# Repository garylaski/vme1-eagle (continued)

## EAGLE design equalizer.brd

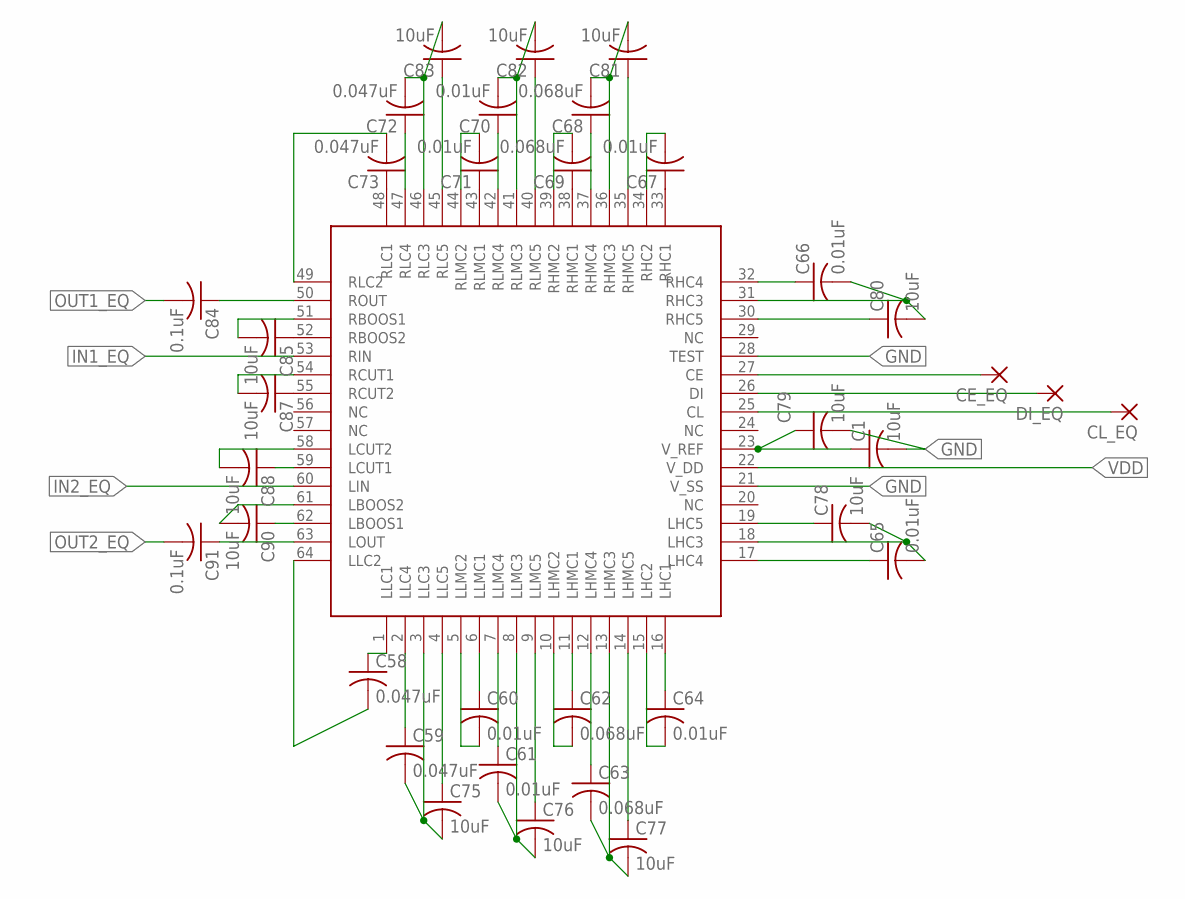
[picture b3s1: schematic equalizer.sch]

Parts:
C1, C75, C76, C77, C78, C79, C80, C81, C82, C83, C85, C87, C88, C90: 10uF; C0402
C58, C59, C72, C73: 0.047uF; C0402
C60, C61, C64, C65, C66, C67, C70, C71: 0.01uF; C0402
C62, C63, C68, C69: 0.068uF; C0402
C84, C91: 0.1uF; C0402
CE_EQ: SMD2; SMD1,27-2,54
CL_EQ: SMD2; SMD1,27-2,54
DI_EQ: SMD2; SMD1,27-2,54
U$14: LC75281E; QFP80P1720X1720X270-64N

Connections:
EQ1_CE: CE_EQ.1, U$14.27 (CE)
EQ1_CL: CL_EQ.1, U$14.25 (CL)
EQ1_DI: DI_EQ.1, U$14.26 (DI)
GND: C1.2, C79.2, U$14.21 (V_SS), U$14.28 (TEST)
IN1_EQ: U$14.53 (RIN)
IN2_EQ: U$14.60 (LIN)
unnamed: C59.1, U$14.2 (LLC4)
unnamed: C58.1, U$14.1 (LLC1)
unnamed: C60.1, U$14.6 (LLMC1)
unnamed: C61.1, U$14.7 (LLMC4)
unnamed: C62.1, U$14.11 (LHMC1)
unnamed: C63.1, U$14.12 (LHMC4)
unnamed: C64.1, U$14.16 (LHC1)
unnamed: C65.1, U$14.17 (LHC4)
unnamed: C66.1, U$14.32 (RHC4)
unnamed: C67.1, U$14.33 (RHC1)
unnamed: C68.1, U$14.37 (RHMC4)
unnamed: C69.1, U$14.38 (RHMC1)
unnamed: C70.1, U$14.42 (RLMC4)
unnamed: C71.1, U$14.43 (RLMC1)
unnamed: C72.1, U$14.47 (RLC4)
unnamed: C73.1, U$14.48 (RLC1)
unnamed: C58.2, U$14.64 (LLC2)
unnamed: C59.2, C75.2, U$14.3 (LLC3)
unnamed: C75.1, U$14.4 (LLC5)
unnamed: C76.1, U$14.9 (LLMC5)
unnamed: C77.1, U$14.14 (LHMC5)
unnamed: C78.1, U$14.19 (LHC5)
unnamed: C1.1, C79.1, U$14.23 (V_REF)
unnamed: C80.1, U$14.30 (RHC5)
unnamed: C81.1, U$14.35 (RHMC5)
unnamed: C82.1, U$14.40 (RLMC5)
unnamed: C83.1, U$14.45 (RLC5)
unnamed: C84.1, U$14.50 (ROUT)
unnamed: C85.1, U$14.52 (RBOOS2)
unnamed: C87.1, U$14.55 (RCUT2)
unnamed: C88.1, U$14.59 (LCUT1)
unnamed: C90.1, U$14.62 (LBOOS1)
unnamed: C91.1, U$14.63 (LOUT)
unnamed: C60.2, U$14.5 (LLMC2)
unnamed: C61.2, C76.2, U$14.8 (LLMC3)
unnamed: C62.2, U$14.10 (LHMC2)
unnamed: C63.2, C77.2, U$14.13 (LHMC3)
unnamed: C64.2, U$14.15 (LHC2)
unnamed: C65.2, C78.2, U$14.18 (LHC3)
unnamed: C66.2, C80.2, U$14.31 (RHC3)
unnamed: C67.2, U$14.34 (RHC2)
unnamed: C68.2, C81.2, U$14.36 (RHMC3)
unnamed: C69.2, U$14.39 (RHMC2)
unnamed: C70.2, C82.2, U$14.41 (RLMC3)
unnamed: C71.2, U$14.44 (RLMC2)
unnamed: C72.2, C83.2, U$14.46 (RLC3)
unnamed: C73.2, U$14.49 (RLC2)
unnamed: C85.2, U$14.51 (RBOOS1)
unnamed: C87.2, U$14.54 (RCUT1)
unnamed: C88.2, U$14.58 (LCUT2)
unnamed: C90.2, U$14.61 (LBOOS2)
OUT1_EQ: C84.2
OUT2_EQ: C91.2
VDD: U$14.22 (V_DD)

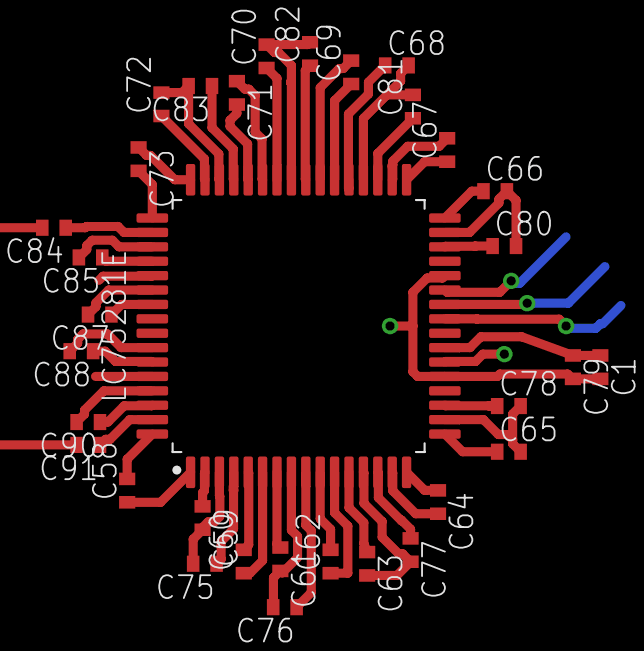
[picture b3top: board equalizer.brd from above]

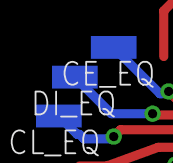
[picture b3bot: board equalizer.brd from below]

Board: 4 copper layers, 36 parts (3 on the bottom side), 55 nets.

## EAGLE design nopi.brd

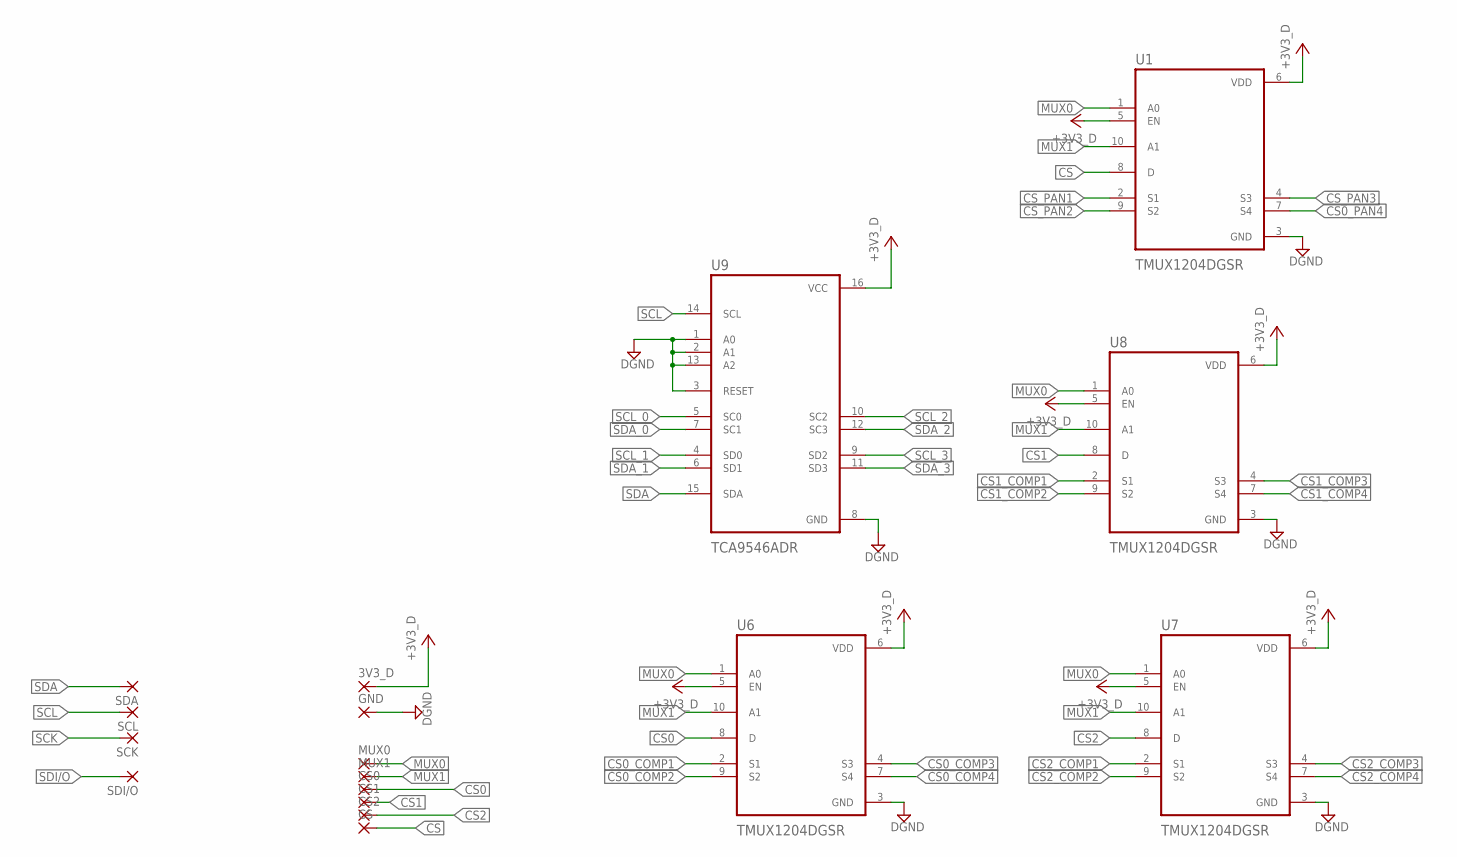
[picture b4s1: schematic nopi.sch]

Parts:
3V3_D: SMD2; SMD1,27-2,54
CS, CS0, CS1, CS2: SMD2; SMD1,27-2,54
GND: SMD2; SMD1,27-2,54
MUX0, MUX1: SMD2; SMD1,27-2,54
SCK: SMD2; SMD1,27-2,54
SCL: SMD2; SMD1,27-2,54
SDA: SMD2; SMD1,27-2,54
SDI/O: SMD2; SMD1,27-2,54
U1, U6, U7, U8: TMUX1204DGSR; SOP50P490X110-10N
U9: TCA9546ADR; SOIC127P600X175-16N

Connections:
+3V3: 3V3_D.1, U1.5 (EN), U1.6 (VDD), U6.5 (EN), U6.6 (VDD), U7.5 (EN), U7.6 (VDD), U8.5 (EN), U8.6 (VDD), U9.16 (VCC)
CS: CS.1, U1.8 (D)
CS0: CS0.1, U6.8 (D)
CS0_COMP1: U6.2 (S1)
CS0_COMP2: U6.9 (S2)
CS0_COMP3: U6.4 (S3)
CS0_COMP4: U6.7 (S4)
CS0_PAN4: U1.7 (S4)
CS1: CS1.1, U8.8 (D)
CS1_COMP1: U8.2 (S1)
CS1_COMP2: U8.9 (S2)
CS1_COMP3: U8.4 (S3)
CS1_COMP4: U8.7 (S4)
CS2: CS2.1, U7.8 (D)
CS2_COMP1: U7.2 (S1)
CS2_COMP2: U7.9 (S2)
CS2_COMP3: U7.4 (S3)
CS2_COMP4: U7.7 (S4)
CS_PAN1: U1.2 (S1)
CS_PAN2: U1.9 (S2)
CS_PAN3: U1.4 (S3)
DGND: GND.1, U1.3 (GND), U6.3 (GND), U7.3 (GND), U8.3 (GND), U9.1 (A0), U9.2 (A1), U9.3 (RESET), U9.8 (GND), U9.13 (A2)
MUX0: MUX0.1, U1.1 (A0), U6.1 (A0), U7.1 (A0), U8.1 (A0)
MUX1: MUX1.1, U1.10 (A1), U6.10 (A1), U7.10 (A1), U8.10 (A1)
SCK: SCK.1
SCL: SCL.1, U9.14 (SCL)
SCL_0: U9.5 (SC0)
SCL_1: U9.4 (SD0)
SCL_2: U9.10 (SC2)
SCL_3: U9.9 (SD2)
SDA: SDA.1, U9.15 (SDA)
SDA_0: U9.7 (SC1)
SDA_1: U9.6 (SD1)
SDA_2: U9.12 (SC3)
SDA_3: U9.11 (SD3)
SDI/O: SDI/O.1

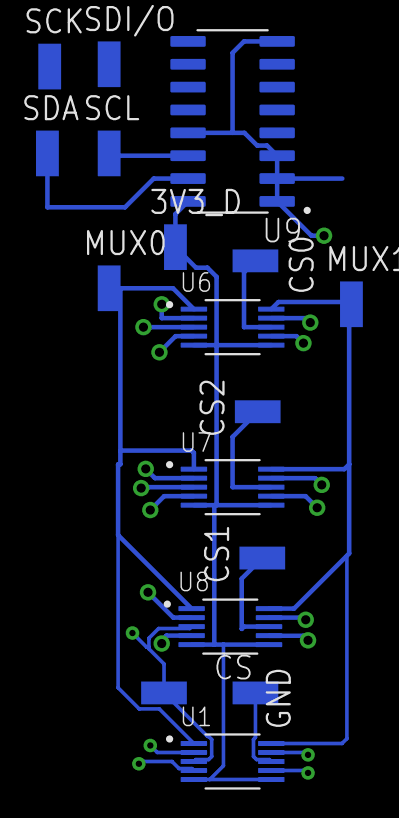
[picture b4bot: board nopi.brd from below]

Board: 4 copper layers, 17 parts (17 on the bottom side), 10 nets.

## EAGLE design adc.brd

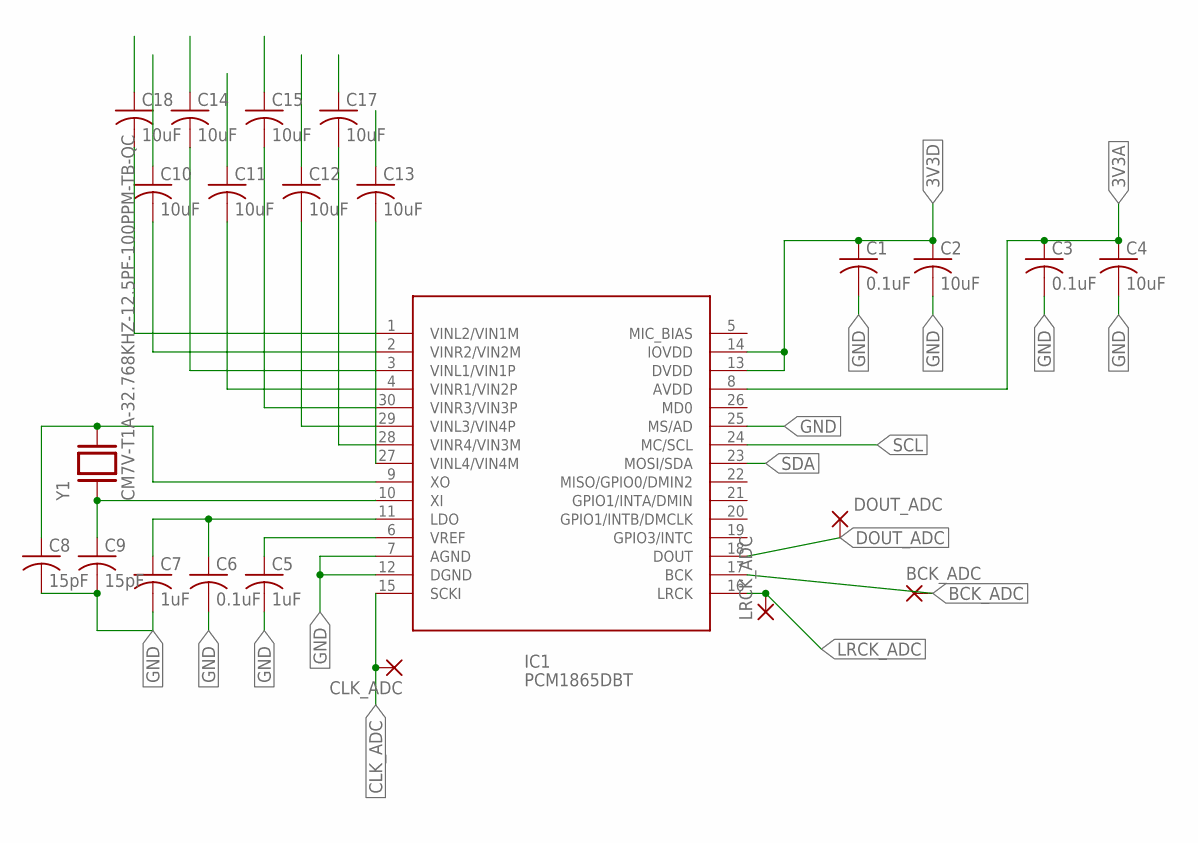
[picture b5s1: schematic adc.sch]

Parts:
BCK_ADC: SMD2; SMD1,27-2,54
C1, C3, C6: 0.1uF; C0402
C2, C4, C10, C11, C12, C13, C14, C15, C17, C18: 10uF; C0402
C5, C7: 1uF; C0402
C8, C9: 15pF; C0402
CLK_ADC: SMD2; SMD1,27-2,54
DOUT_ADC: SMD2; SMD1,27-2,54
IC1: PCM1865DBT; TSSOP-30
LRCK_ADC: SMD2; SMD1,27-2,54
Y1: CM7V-T1A-32.768KHZ-12.5PF-100PPM-TB-QC; XTAL_CM7V-T1A-32.768KHZ-12.5PF-100PPM-TB-QC

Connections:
3V3A: C3.1, C4.1, IC1.8 (AVDD)
3V3D: C1.1, C2.1, IC1.13 (DVDD), IC1.14 (IOVDD)
BCK_ADC: BCK_ADC.1, IC1.17 (BCK)
CLK_ADC: CLK_ADC.1, IC1.15 (SCKI)
DOUT_ADC: DOUT_ADC.1, IC1.18 (DOUT)
GND: C1.2, C2.2, C3.2, C4.2, C5.2, C6.2, C7.2, C8.2, C9.2, IC1.7 (AGND), IC1.12 (DGND), IC1.25 (MS/AD)
LRCK_ADC: IC1.16 (LRCK), LRCK_ADC.1
unnamed: C8.1, IC1.9 (XO), Y1.2
unnamed: C9.1, IC1.10 (XI), Y1.1
unnamed: C18.2, IC1.1 (VINL2/VIN1M)
unnamed: C10.2, IC1.2 (VINR2/VIN2M)
unnamed: C14.2, IC1.3 (VINL1/VIN1P)
unnamed: C11.2, IC1.4 (VINR1/VIN2P)
unnamed: C12.2, IC1.29 (VINL3/VIN4P)
unnamed: C5.1, IC1.6 (VREF)
unnamed: C6.1, C7.1, IC1.11 (LDO)
unnamed: C17.2, IC1.28 (VINR4/VIN3M)
unnamed: C13.2, IC1.27 (VINL4/VIN4M)
unnamed: C15.2, IC1.30 (VINR3/VIN3P)
SCL: IC1.24 (MC/SCL)
SDA: IC1.23 (MOSI/SDA)

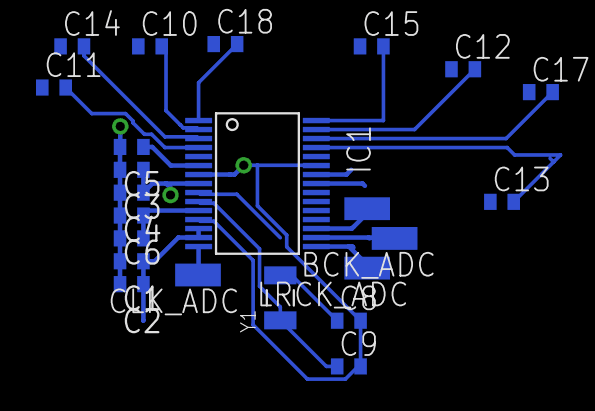
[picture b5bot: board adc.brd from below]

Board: 4 copper layers, 23 parts (23 on the bottom side), 19 nets.

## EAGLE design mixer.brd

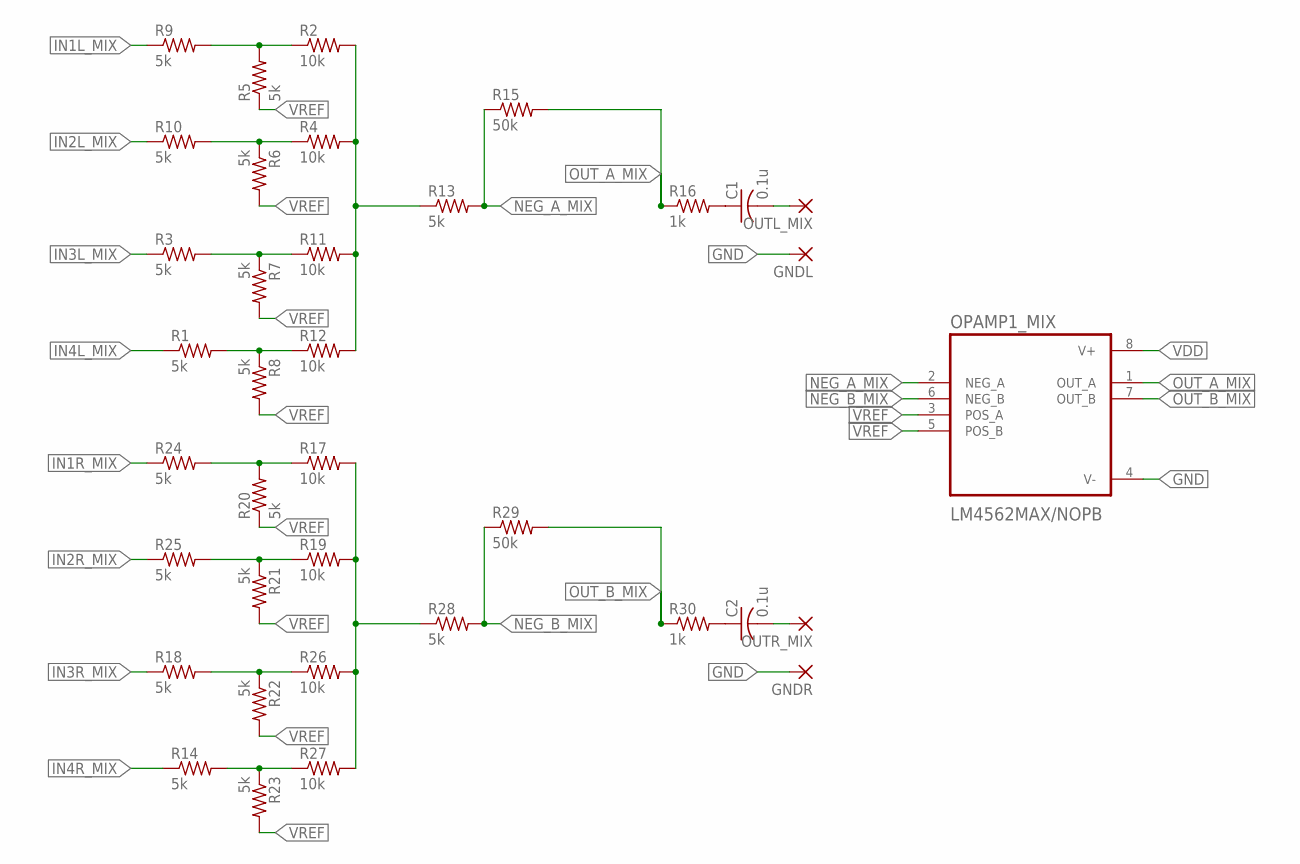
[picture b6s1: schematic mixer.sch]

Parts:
C1, C2: 0.1u; C0402
GNDL: SMD5; SMD2,54-5,08
GNDR: SMD5; SMD2,54-5,08
OPAMP1_MIX: LM4562MAX/NOPB; SOIC127P599X175-8N
OUTL_MIX: SMD5; SMD2,54-5,08
OUTR_MIX: SMD5; SMD2,54-5,08
R1, R3, R5, R6, R7, R8, R9, R10, R13, R14, R18, R20, R21, R22, R23, R24, R25, R28: 5k; R0402
R2, R4, R11, R12, R17, R19, R26, R27: 10k; R0402
R15, R29: 50k; R0402
R16, R30: 1k; R0402

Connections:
GND: GNDL.1, GNDR.1, OPAMP1_MIX.4 (V-)
IN1L_MIX: R9.1
IN1R_MIX: R24.1
IN2L_MIX: R10.1
IN2R_MIX: R25.1
IN3L_MIX: R3.1
IN3R_MIX: R18.1
IN4L_MIX: R1.1
IN4R_MIX: R14.1
unnamed: C1.1, R16.2
unnamed: C2.1, R30.2
unnamed: R17.1, R20.2, R24.2
unnamed: R17.2, R19.2, R26.2, R27.2, R28.1
unnamed: R14.2, R23.1, R27.1
unnamed: R18.2, R22.1, R26.1
unnamed: R19.1, R21.1, R25.2
unnamed: R2.1, R5.2, R9.2
unnamed: R2.2, R4.2, R11.2, R12.2, R13.1
unnamed: R1.2, R8.1, R12.1
unnamed: R3.2, R7.1, R11.1
unnamed: R4.1, R6.1, R10.2
NEG_A_MIX: OPAMP1_MIX.2 (NEG_A), R13.2, R15.1
NEG_B_MIX: OPAMP1_MIX.6 (NEG_B), R28.2, R29.1
OUTL_MIX: C1.2, OUTL_MIX.1
OUTR_MIX: C2.2, OUTR_MIX.1
OUT_A_MIX: OPAMP1_MIX.1 (OUT_A), R15.2, R16.1
OUT_B_MIX: OPAMP1_MIX.7 (OUT_B), R29.2, R30.1
VDD: OPAMP1_MIX.8 (V+)
VREF: OPAMP1_MIX.3 (POS_A), OPAMP1_MIX.5 (POS_B), R5.1, R6.2, R7.2, R8.2, R20.1, R21.2, R22.2, R23.2

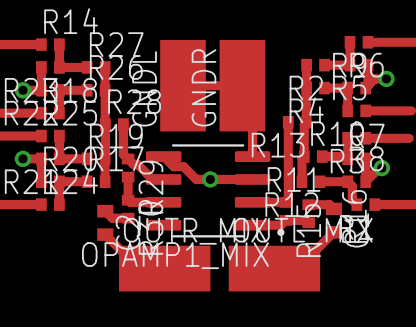
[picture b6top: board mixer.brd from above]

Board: 4 copper layers, 37 parts (0 on the bottom side), 20 nets.

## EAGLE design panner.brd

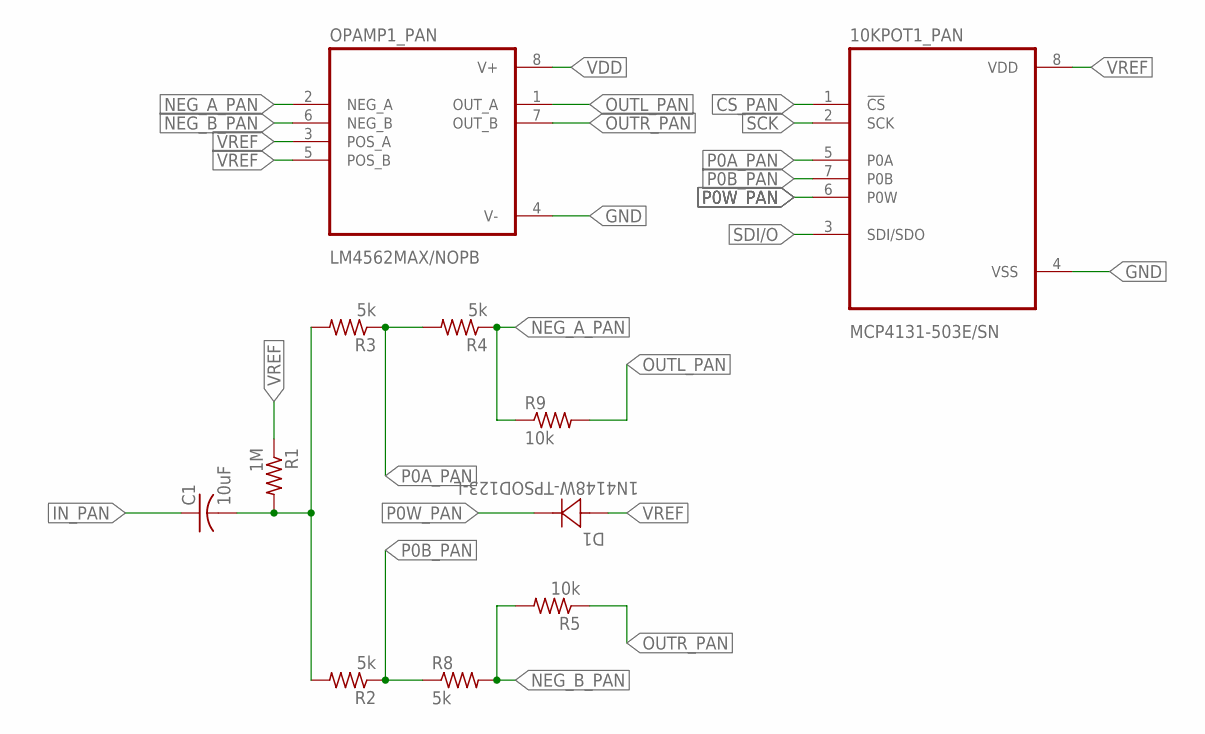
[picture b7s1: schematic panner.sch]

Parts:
10KPOT1_PAN: MCP4131-503E/SN; SOIC127P599X175-8N
C1: 10uF; C0402
D1: 1N4148W-TPSOD123-L; SOD123-L
OPAMP1_PAN: LM4562MAX/NOPB; SOIC127P599X175-8N
R1: 1M; R0402
R2, R3, R4, R8: 5k; R0402
R5, R9: 10k; R0402

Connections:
CS_PAN: 10KPOT1_PAN.1 (!CS)
GND: 10KPOT1_PAN.4 (VSS), OPAMP1_PAN.4 (V-)
IN_PAN: C1.1
unnamed: C1.2, R1.2, R2.2, R3.2
NEG_A_PAN: OPAMP1_PAN.2 (NEG_A), R4.1, R9.1
NEG_B_PAN: OPAMP1_PAN.6 (NEG_B), R5.2, R8.2
OUTL_PAN: OPAMP1_PAN.1 (OUT_A), R9.2
OUTR_PAN: OPAMP1_PAN.7 (OUT_B), R5.1
P0A_PAN: 10KPOT1_PAN.5 (P0A), R3.1, R4.2
P0B_PAN: 10KPOT1_PAN.7 (P0B), R2.1, R8.1
P0W_PAN: 10KPOT1_PAN.6 (P0W), D1.1 (C)
SCK: 10KPOT1_PAN.2 (SCK)
SDI/O: 10KPOT1_PAN.3 (SDI/SDO)
VDD: OPAMP1_PAN.8 (V+)
VREF: 10KPOT1_PAN.8 (VDD), D1.2 (A), OPAMP1_PAN.3 (POS_A), OPAMP1_PAN.5 (POS_B), R1.1

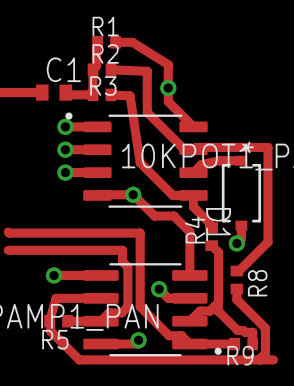
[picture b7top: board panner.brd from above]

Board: 4 copper layers, 11 parts (0 on the bottom side), 10 nets.

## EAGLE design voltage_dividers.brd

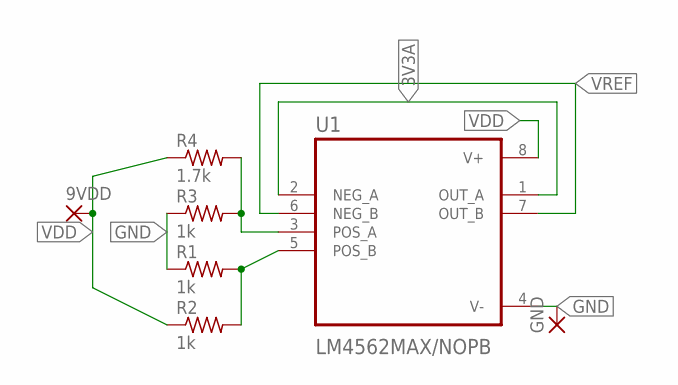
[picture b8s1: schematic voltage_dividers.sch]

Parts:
9VDD: SMD2; SMD1,27-2,54
GND: SMD2; SMD1,27-2,54
R1, R2, R3: 1k; R0402
R4: 1.7k; R0402
U1: LM4562MAX/NOPB; SOIC127P599X175-8N

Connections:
3V3A: U1.1 (OUT_A), U1.2 (NEG_A)
GND: GND.1, R1.1, R3.1, U1.4 (V-)
unnamed: R3.2, R4.2, U1.3 (POS_A)
unnamed: R1.2, R2.2, U1.5 (POS_B)
VDD: 9VDD.1, R2.1, R4.1, U1.8 (V+)
VREF: U1.6 (NEG_B), U1.7 (OUT_B)

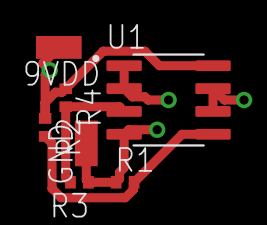
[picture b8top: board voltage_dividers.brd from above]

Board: 4 copper layers, 7 parts (0 on the bottom side), 6 nets.

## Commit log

2023-10-11 Start compressor circuit
2023-10-11 Update compressor schematic
2023-10-18 update compressor with digital pots Added to man schem with muxes
2023-10-18 add other 2 comps and 1 other eq
2023-10-20 update, split out into schematics for each component
2023-10-22 rm cache files, add boards for components
2023-10-22 remove cache files
2023-10-23 finish compressor routing, and sloppy combined routing
2023-10-24 corrections
2023-10-30 v2 of board finished
2023-10-30 update footprint names of MAX5419 for LMNP variants
2023-10-30 update CAM
2023-10-30 clean CAMOutputs
2023-10-30 fixes and export using jlcpcb ulp
2023-10-30 fix on cap units
2023-10-31 new csv
2023-10-31 update rest of gerber
2023-10-31 update csvs again
2023-11-01 update power resisitors
2023-11-08 replace incorrect diode size
2023-11-08 correct csvs
2023-11-08 update bor format
